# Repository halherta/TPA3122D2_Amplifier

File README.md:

# TPA3122D2 Class D Amplifier

A stereo 15W + 15W, all through-hole Class D amplifier board built around the Texas Instruments [TPA3122D2](https://www.ti.com/lit/ds/symlink/tpa3122d2.pdf), designed in KiCad. The board is also compatible with the pin-compatible [TPA3125D2](https://www.ti.com/lit/ds/symlink/tpa3125d2.pdf) (10W stereo).

## Overview

The TPA3122D2 is, to the author's knowledge, the only through-hole Class D amplifier IC. It comes in a 20-pin DIP package and needs only a relatively simple LC filter on its output. That makes this board a good fit for:

- A beginner-friendly soldering kit
- Learning PCB layout in KiCad (start from the provided schematic and draw your own layout)
- A compact, efficient stereo amplifier for passive speakers

**A note on part availability:** the TPA3122D2 is listed as *Active* on the TI site, but there are reports that it will move to *Not Recommended for New Designs*. The TPA3125D2 is a pin-compatible through-hole drop-in that is expected to stay active longer. It is nearly identical, except its output is rated for 10W (stereo) instead of 15W. This board can be used with either IC.

## Features

- Stereo output: 15W + 15W (TPA3122D2) or 10W + 10W (TPA3125D2)
- Supply voltage: 10 to 30 V
- Power input through a screw terminal block or a DC barrel jack
- Reverse-polarity protection on the power rails
- 3.5 mm audio jack input
- Dual-gang potentiometer for volume control of both channels
- Output LC filter as recommended in the datasheet
- 4-pin terminal block for left and right passive speakers
- Generous bypass capacitors on the supply rails and outputs
- Two SPST switches for **shutdown** and **mute** using the IC's control pins
- All through-hole parts
- 2-layer PCB, 80 mm x 80 mm

## Schematic and Layout

The schematic closely follows the recommended application circuit in the TPA3122D2 datasheet.

| Schematic | Layout | 3D View |
|---|---|---|
| [Schematic](https://github.com/halherta/TPA3122D2_Amplifier/blob/main/images/TPA3122D2_AmplifierSchematic.png) |  |  |

- [high quality version of the schematic (pdf)](https://github.com/halherta/TPA3122D2_Amplifier/blob/main/images/TPA3122D2_Amplifier.pdf)
- [high quality version of the schematic (svg)](https://github.com/halherta/TPA3122D2_Amplifier/blob/main/images/TPA3122D2_Amplifier.svg)
  
## Repository Contents

| Path | Description |
|---|---|
| `TPA3122D2_Amplifier.kicad_pro` | KiCad project file |
| `TPA3122D2_Amplifier.kicad_sch` | Schematic |
| `TPA3122D2_Amplifier.kicad_pcb` | PCB layout |
| `TPA3122D2_Amplifier.kicad_prl` | KiCad local project settings |
| `Gerbers/` | Gerber and drill files for fabrication |
| `TPA3122D2LatestGerbers.zip` | Zipped Gerbers, ready to upload to a PCB fab |
| `DigikeyBom/` | Bill of materials for ordering from Digi-Key |
| `fp-info-cache` | KiCad footprint library cache |

## Getting Started

### Requirements

- [KiCad](https://www.kicad.org/) to open and edit the design

### Opening the design

1. Clone the repository:
   ```bash
   git clone https://github.com/halherta/TPA3122D2_Amplifier.git
   ```
2. Open `TPA3122D2_Amplifier.kicad_pro` in KiCad.
3. Open the schematic or PCB editor from the project window.

### Ordering the board

1. Upload `TPA3122D2LatestGerbers.zip` to your PCB manufacturer of choice (2-layer, 80 mm x 80 mm).
2. Use the files in `DigikeyBom/` to order components.

### Assembly and use

1. Solder the components, starting with the lowest-profile parts. The IC can be placed in a DIP socket.
2. Connect two passive speakers to the 4-pin output terminal block, observing left/right channel markings on the board.
3. Connect an audio source to the 3.5 mm input jack.
4. Apply a DC supply of 10 to 30 V through the terminal block or barrel jack. An old 19.5 V laptop charger works well.
5. Use the potentiometer to set the volume, and the SPST switches for shutdown and mute.

> **Tip:** Check the TPA3122D2 datasheet for supply voltage versus speaker impedance and output power limits before choosing a power supply and speakers.

## Status

The board has been fabricated, populated, and tested successfully. It amplifies audio well and gives decent sound quality and volume with a good pair of passive speakers.

## Further Reading

- [Design write-up on Hussam Talks Tech](https://hussamtalkstech.com/thruhole_classd_amp_board/)
- [TPA3122D2 datasheet (TI)](https://www.ti.com/lit/ds/symlink/tpa3122d2.pdf)
- [TPA3125D2 datasheet (TI)](https://www.ti.com/lit/ds/symlink/tpa3125d2.pdf)

## Author

[halherta](https://github.com/halherta)

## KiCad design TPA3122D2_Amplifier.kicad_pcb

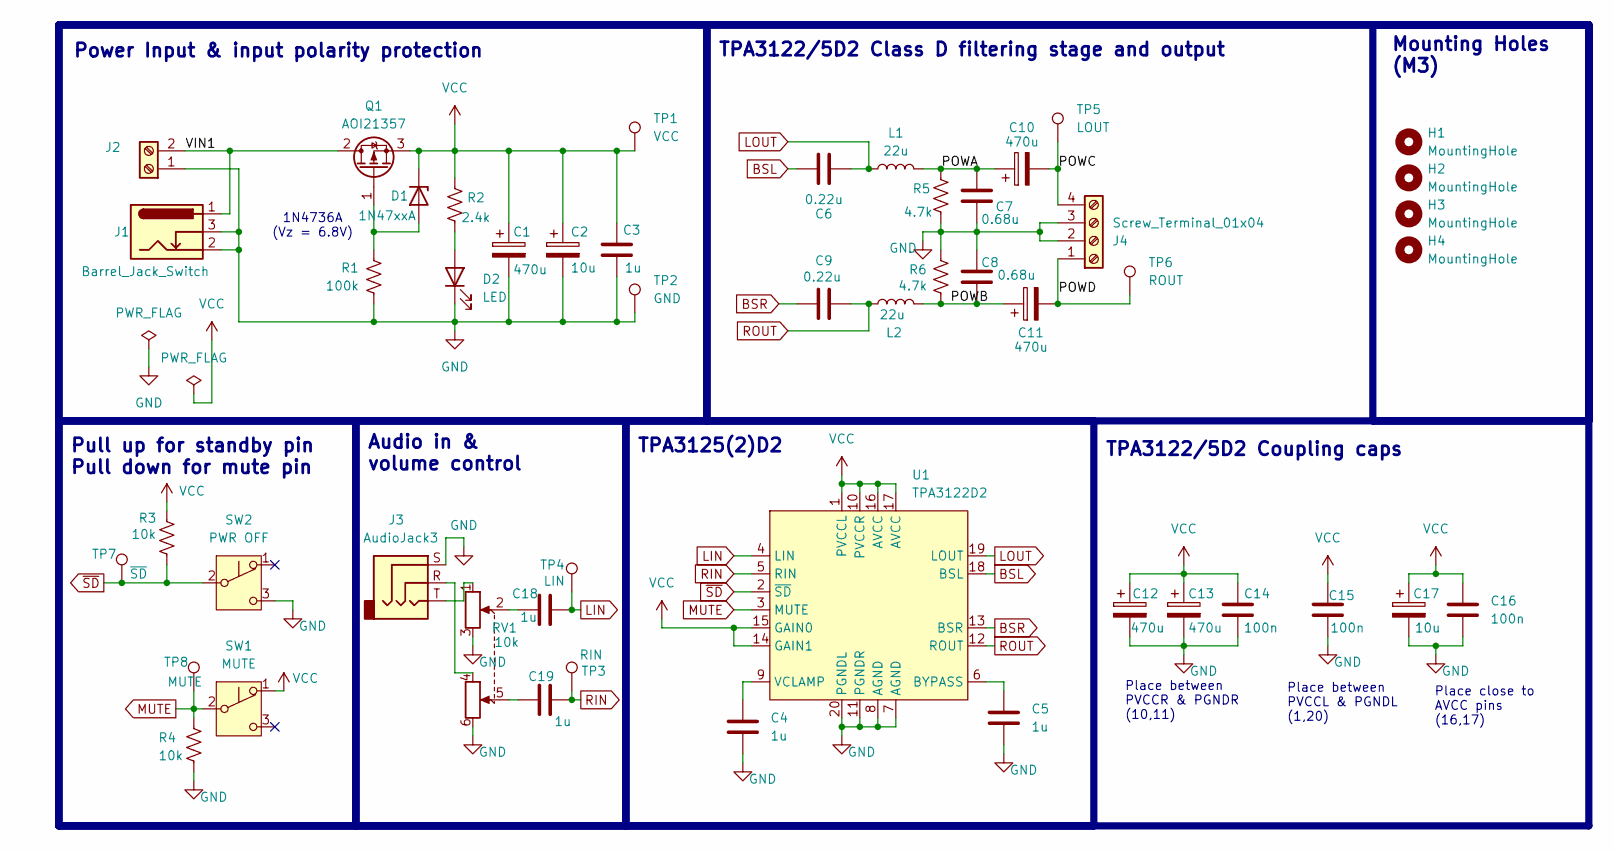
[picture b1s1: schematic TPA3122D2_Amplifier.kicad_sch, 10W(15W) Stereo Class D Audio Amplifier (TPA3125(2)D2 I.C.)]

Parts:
C1, C10, C11, C12, C13: 470u; CP_Radial_D10.0mm_P5.00mm
C2, C17: 10u; CP_Radial_D5.0mm_P2.50mm
C3, C4, C5, C18, C19: 1u; C_Disc_D4.3mm_W1.9mm_P5.00mm
C6, C9: 0.22u; C_Disc_D4.3mm_W1.9mm_P5.00mm
C7, C8: 0.68u; C_Disc_D4.3mm_W1.9mm_P5.00mm
C14, C15, C16: 100n; C_Disc_D4.3mm_W1.9mm_P5.00mm
D1: 1N47xxA; D_DO-41_SOD81_P10.16mm_Horizontal
D2: LED; LED_D5.0mm
H1, H2, H3, H4: MountingHole; MountingHole_3.2mm_M3
J1: Barrel_Jack_Switch; BarrelJack_CUI_PJ-102AH_Horizontal
J2: Screw_Terminal_01x02; TerminalBlock_Phoenix_MKDS-1,5-2_1x02_P5.00mm_Horizontal
J3: AudioJack3; Jack_3.5mm_CUI_SJ1-3523N_Horizontal
J4: Screw_Terminal_01x04; TerminalBlock_Phoenix_MKDS-1,5-4_1x04_P5.00mm_Horizontal
L1, L2: 22u; L_Radial_D10.0mm_P5.00mm_Fastron_07M
Q1: AOI21357; TO-251-3_Vertical
R1: 100k; R_Axial_DIN0207_L6.3mm_D2.5mm_P10.16mm_Horizontal
R2: 2.4k; R_Axial_DIN0207_L6.3mm_D2.5mm_P10.16mm_Horizontal
R3, R4: 10k; R_Axial_DIN0207_L6.3mm_D2.5mm_P10.16mm_Horizontal
R5, R6: 4.7k; R_Axial_DIN0207_L6.3mm_D2.5mm_P10.16mm_Horizontal
RV1: 10k; PTD902-2015K-B103
SW1: MUTE; SW_E-Switch_EG1224_SPDT_Angled
SW2: PWR OFF; SW_E-Switch_EG1224_SPDT_Angled
TP1: VCC; TestPoint_THTPad_D2.0mm_Drill1.0mm
TP2: GND; TestPoint_THTPad_D2.0mm_Drill1.0mm
TP3: RIN; TestPoint_THTPad_D2.0mm_Drill1.0mm
TP4: LIN; TestPoint_THTPad_D2.0mm_Drill1.0mm
TP5: LOUT; TestPoint_THTPad_D2.0mm_Drill1.0mm
TP6: ROUT; TestPoint_THTPad_D2.0mm_Drill1.0mm
TP7: ~{SD}; TestPoint_THTPad_D2.0mm_Drill1.0mm
TP8: MUTE; TestPoint_THTPad_D2.0mm_Drill1.0mm
U1: TPA3122D2; DIP-20_W7.62mm_LongPads

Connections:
/POWA: C7.1, C10.1, L1.2, R5.1
/POWB: C8.2, C11.1, L2.2, R6.2
/POWC: C10.2, J4.4, TP5.1 (1_1)
/POWD: C11.2, J4.1, TP6.1 (1_1)
/VIN1: J1.1, J2.2, Q1.2 (D)
BSL: C6.2, U1.18 (BSL)
BSR: C9.2, U1.13 (BSR)
GND: C1.2, C2.2, C3.2, C4.2, C5.2, C7.2, C8.1, C12.2, C13.2, C14.2, C15.2, C16.2, C17.2, D2.1 (K), J1.2, J1.3, J2.1, J3.S, J4.2, J4.3, R1.2, R4.2, R5.2, R6.1, RV1.3, RV1.6, SW2.3 (C), TP2.1 (1_1), U1.7 (AGND), U1.8 (AGND), U1.11 (PGNDR), U1.20 (PGNDL)
LIN: C18.2, TP4.1 (1_1), U1.4 (LIN)
LOUT: C6.1, L1.1, U1.19 (LOUT)
MUTE: R4.1, SW1.2 (B), TP8.1 (1_1), U1.3 (MUTE)
unnamed: C18.1, RV1.2
unnamed: C19.1, RV1.5
unnamed: D1.2 (A), Q1.1 (G), R1.1
unnamed: D2.2 (A), R2.2
unnamed: J3.R, RV1.4
unnamed: J3.T, RV1.1
unnamed: C5.1, U1.6 (BYPASS)
unnamed: C4.1, U1.9 (VCLAMP)
RIN: C19.2, TP3.1 (1_1), U1.5 (RIN)
ROUT: C9.1, L2.1, U1.12 (ROUT)
VCC: C1.1, C2.1, C3.1, C12.1, C13.1, C14.1, C15.1, C16.1, C17.1, D1.1 (K), Q1.3 (S), R2.1, R3.1, SW1.1 (A), TP1.1 (1_1), U1.1 (PVCCL), U1.10 (PVCCR), U1.14 (GAIN1), U1.15 (GAIN0), U1.16 (AVCC), U1.17 (AVCC)
~SD: R3.2, SW2.2 (B), TP7.1 (1_1), U1.2 (~SD)

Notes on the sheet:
1N4736A (Vz = 6.8V)
Audio in & volume control
Power Input & input polarity protection
TPA3122/5D2 Coupling caps
Mounting Holes (M3)
TPA3125(2)D2
Place between PVCCR & PGNDR (10,11)
Place between PVCCL & PGNDL (1,20)
Place close to AVCC pins (16,17)
TPA3122/5D2 Class D filtering stage and output
Pull up for standby pin Pull down for mute pin

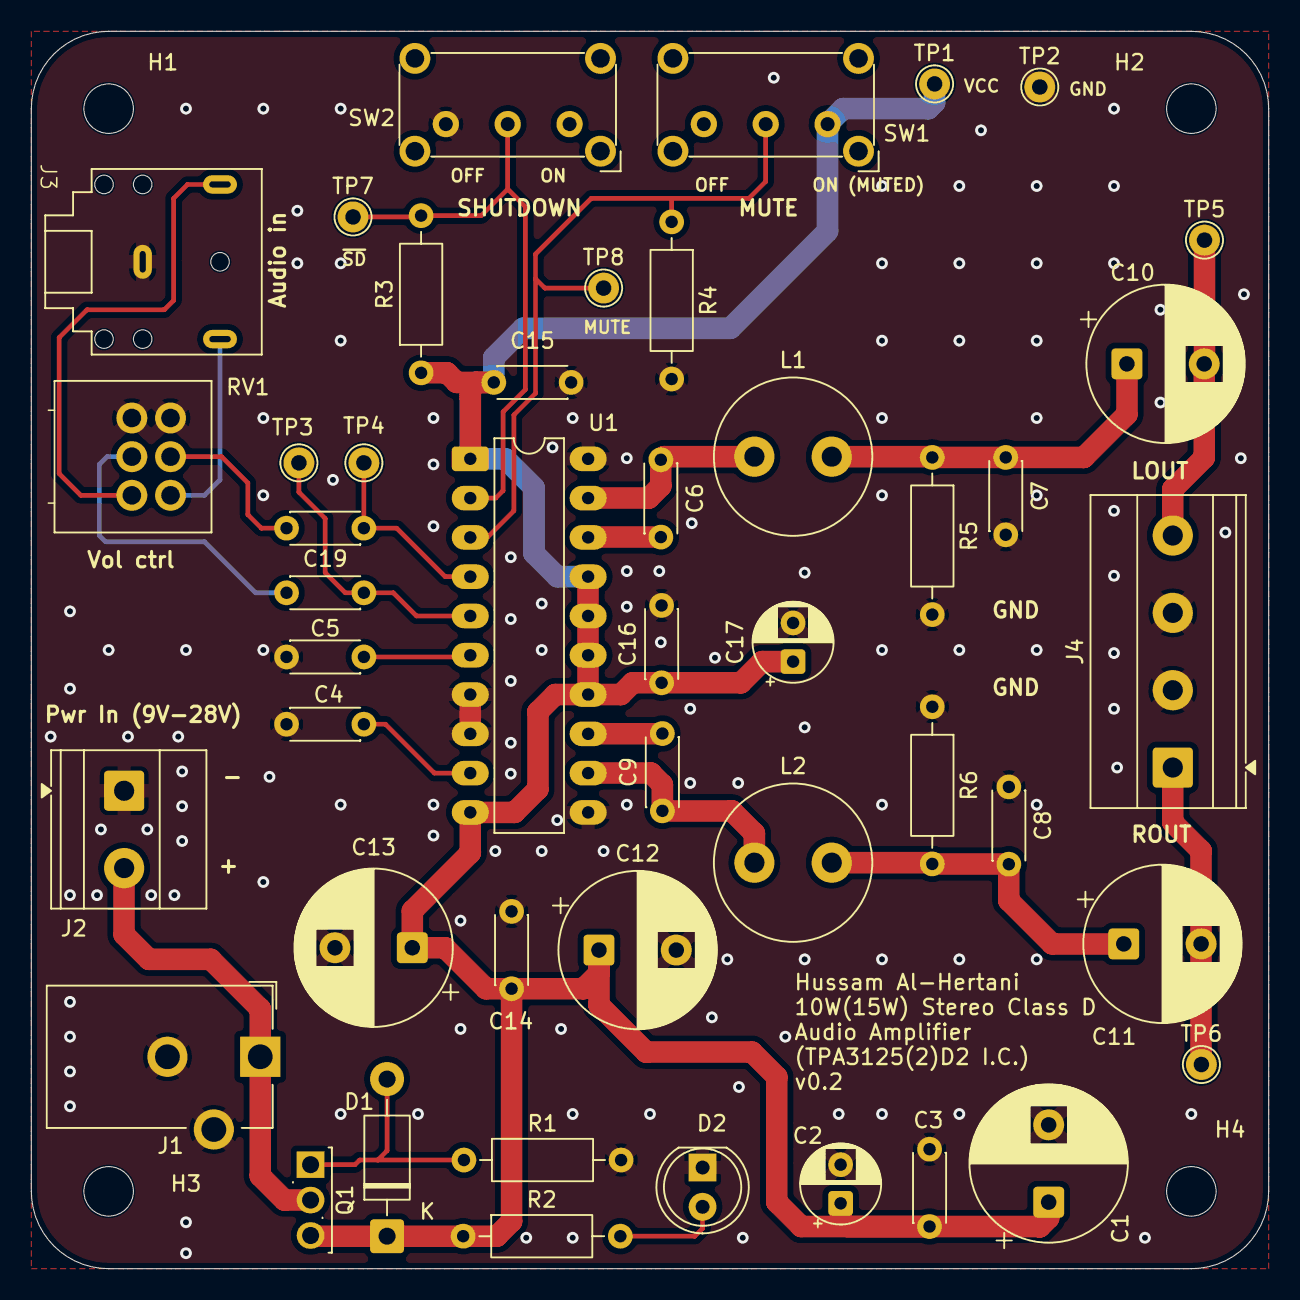
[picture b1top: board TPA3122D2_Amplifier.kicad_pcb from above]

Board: 2 copper layers, 80.0 x 80.0 mm, 50 parts (0 on the bottom side), 23 nets.

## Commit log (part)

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2024-11-07 fixed misplaced capacitors C6 & C9
2025-09-22 updated audio connector
2025-09-22 fixed terminal blocks
